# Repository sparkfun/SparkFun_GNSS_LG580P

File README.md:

SparkFun Quadband GNSS RTK with Heading Breakout - LG580P (Qwiic)
========================================

[*SparkFun Quadband GNSS RTK with Heading Breakout - LG580P (Qwiic) (GPS-28019)*](https://www.sparkfun.com/sparkfun-quadband-gnss-rtk-with-heading-breakout-lg580p-qwiic.html)

The [SparkFun Quadband GNSS RTK with Heading Breakout - LG580P (Qwiic)](https://www.sparkfun.com/sparkfun-quadband-gnss-rtk-with-heading-breakout-lg580p-qwiic.html) features the Quectel LG580P GNSS module, providing exceptional positioning and heading accuracy. The LG580P GNSS module is an upgraded version of the LG290P on our [SparkFun Quadband GNSS RTK Breakout - LG290P (Qwiic)](https://www.sparkfun.com/sparkfun-quadband-gnss-rtk-breakout-lg290p-qwiic.html); providing an additional GNSS antenna input for instantaneous heading determination down to 0.1&deg;. In traditional navigation systems, such as those used on your phone or car, previous navigation points are utilized to determine the course heading. This is the reason why the arrow indicator will spin or be oriented in the wrong directions when the navigation system first boots or has been stationary for extended periods of time. However, with the LG580 GNSS module, users are provided with a dedicated heading without relying on previous course data points, magnetometers/compasses, or gyroscopes in IMUs, which can introduce small errors.

The board's dimensions, pin layout, and connectors are similar to our very popular [SparkFun GPS-RTK-SMA Breakout - ZED-F9P (Qwiic)](https://www.sparkfun.com/sparkfun-gps-rtk-sma-breakout-zed-f9p-qwiic.html), featuring a compact design and convenient Qwiic connectors. *(\*Depending on your application, this board could potentially function as a drop-in replacement; users should verify the pin compatibility of this board with their current installation.)* The board also accommodates users with a diverse choice of interfaces including UART, SPI*, I<sup>2</sup>C*, and CAN*. The board has three UART ports, which are accessible through the USB-C connector, BlueSMiRF *(6-pin PTH)* header, and 4-pin locking JST connector. Users can also interface with the board through the 25 PTH pins that are broken out around the edge of the board. For the GNSS antenna(s), SMA antenna connectors are provided on the edge of the board; an optional, secondary antenna can be utilized for heading determination. We also provide two 4-pin JST Qwiic connectors for future use, when the I<sup>2</sup>C feature becomes available for the GNSS module.

The LG580P module is a quad-band, multi-constellation, high-precision, RTK and heading GNSS receiver. The module is capable of simultaneously receiving signals from the `L1`, `L2`, `L5`, and `L6`/`E6` frequency bands of the GPS, GLONASS, Galileo, BDS, QZSS, and NavIC GNSS constellations. In addition, the module supports SBAS augmentation systems (WAAS, EGNOS, BDSBAS, MSAS, GAGAN, KASS, ASECNA, SouthPAN, and SDCM), PPP services* (BDS PPP-B2b, QZSS CLAS, MADOCA-PPP, and Galileo HAS), RTCM, and RTK corrections for precision navigation with a fast convergence time and reliable performance.

The built-in professional-grade interference signal detection and elimination algorithms, effectively mitigate multiple narrow-band interference sources and significantly improve signal reception performance in complex electromagnetic environments. In addition, the RTK and heading algorithms ensure reliable positioning in challenging scenarios such as urban environments and deep tree cover. With its high-precision, low power consumption and a high positioning and heading update rate of up to 20 Hz, this board is ideal for high-precision navigation applications, such as intelligent robots, precision agriculture, ADAS, and autonomous driving.

> [!NOTE]
> `*`: Feature is still under development

> [!IMPORTANT]
> - Currently, only the UART interface is supported by the module. All three UART ports are broken out to the USB-C connector *(via CH342 USB-serial converter)*, 4-pin locking JST connector, and BlueSMiRF 6-pin header.
> - Additionally, the corrections for some of the PPP services may not be implemented yet.

Documentation
--------------

- **[Hookup Guide (mkdocs)](http://docs.sparkfun.com/SparkFun_GNSS_LG580P/)** - A hookup guide for the SparkFun Quadband GNSS RTK Breakout - LG580P breakout board hosted by GitHub pages<br>
   
- [SparkFun LG290P GNSS Arduino Library](https://github.com/sparkfun/SparkFun_LG290P_GNSS_Arduino_Library) - An Arduino library for the LG290P and LGx80P GNSS modules

Repository Contents
-------------------

- **[/docs](/docs/)** - Online documentation files
  - [/assets](/docs/assets/) - Assets files
    - [/3d_model](/docs/assets/3d_model/) - 3D models for the board
    - [/board_files](/docs/assets/board_files/) - Design files for the board
      - [KiCad Design Files](/docs/assets/board_files/kicad_files.zip) (.zip)
      - [Schematic](/docs/assets/board_files/schematic.pdf) (.pdf)
      - [Dimensions](/docs/assets/board_files/dimensions.pdf) (.pdf)
    - [/component_documentation](/docs/assets/component_documentation/) - Datasheets for hardware components
    - [/img/hookup_guide](/docs/assets/img/hookup_guide/) - Images for hookup guide documentation - Hookup guide images for the board
    - /Hardware - Hardware design files (.brd, .sch)
      - /Production - Production files

Product Variants
----------------

- [GPS-28019](https://www.sparkfun.com/sparkfun-quadband-gnss-rtk-with-heading-breakout-lg580p-qwiic.html) - v1.0, Initial Release
- LG290P Variants
  - [GPS-26620](https://www.sparkfun.com/sparkfun-quadband-gnss-rtk-breakout-lg290p-qwiic.html) - SparkFun LG290P Breakout
  - [GPS-26916](https://www.sparkfun.com/sparkfun-rtk-postcard.html) - SparkFun RTK Postcard *(LG290P + ESP32)*

Version History
---------------

- [v10](https://github.com/sparkfun/SparkFun_GNSS_LG580P/releases/tag/v10) - Initial Release

License Information
-------------------

This product is ***open source***!

Please review the [`LICENSE.md`](./LICENSE.md) file for license information.

If you have any questions or concerns about licensing, please contact technical support on our [SparkFun forums](https://forum.sparkfun.com/viewforum.php?f=152).

Distributed as-is; no warranty is given.

- Your friends at SparkFun.

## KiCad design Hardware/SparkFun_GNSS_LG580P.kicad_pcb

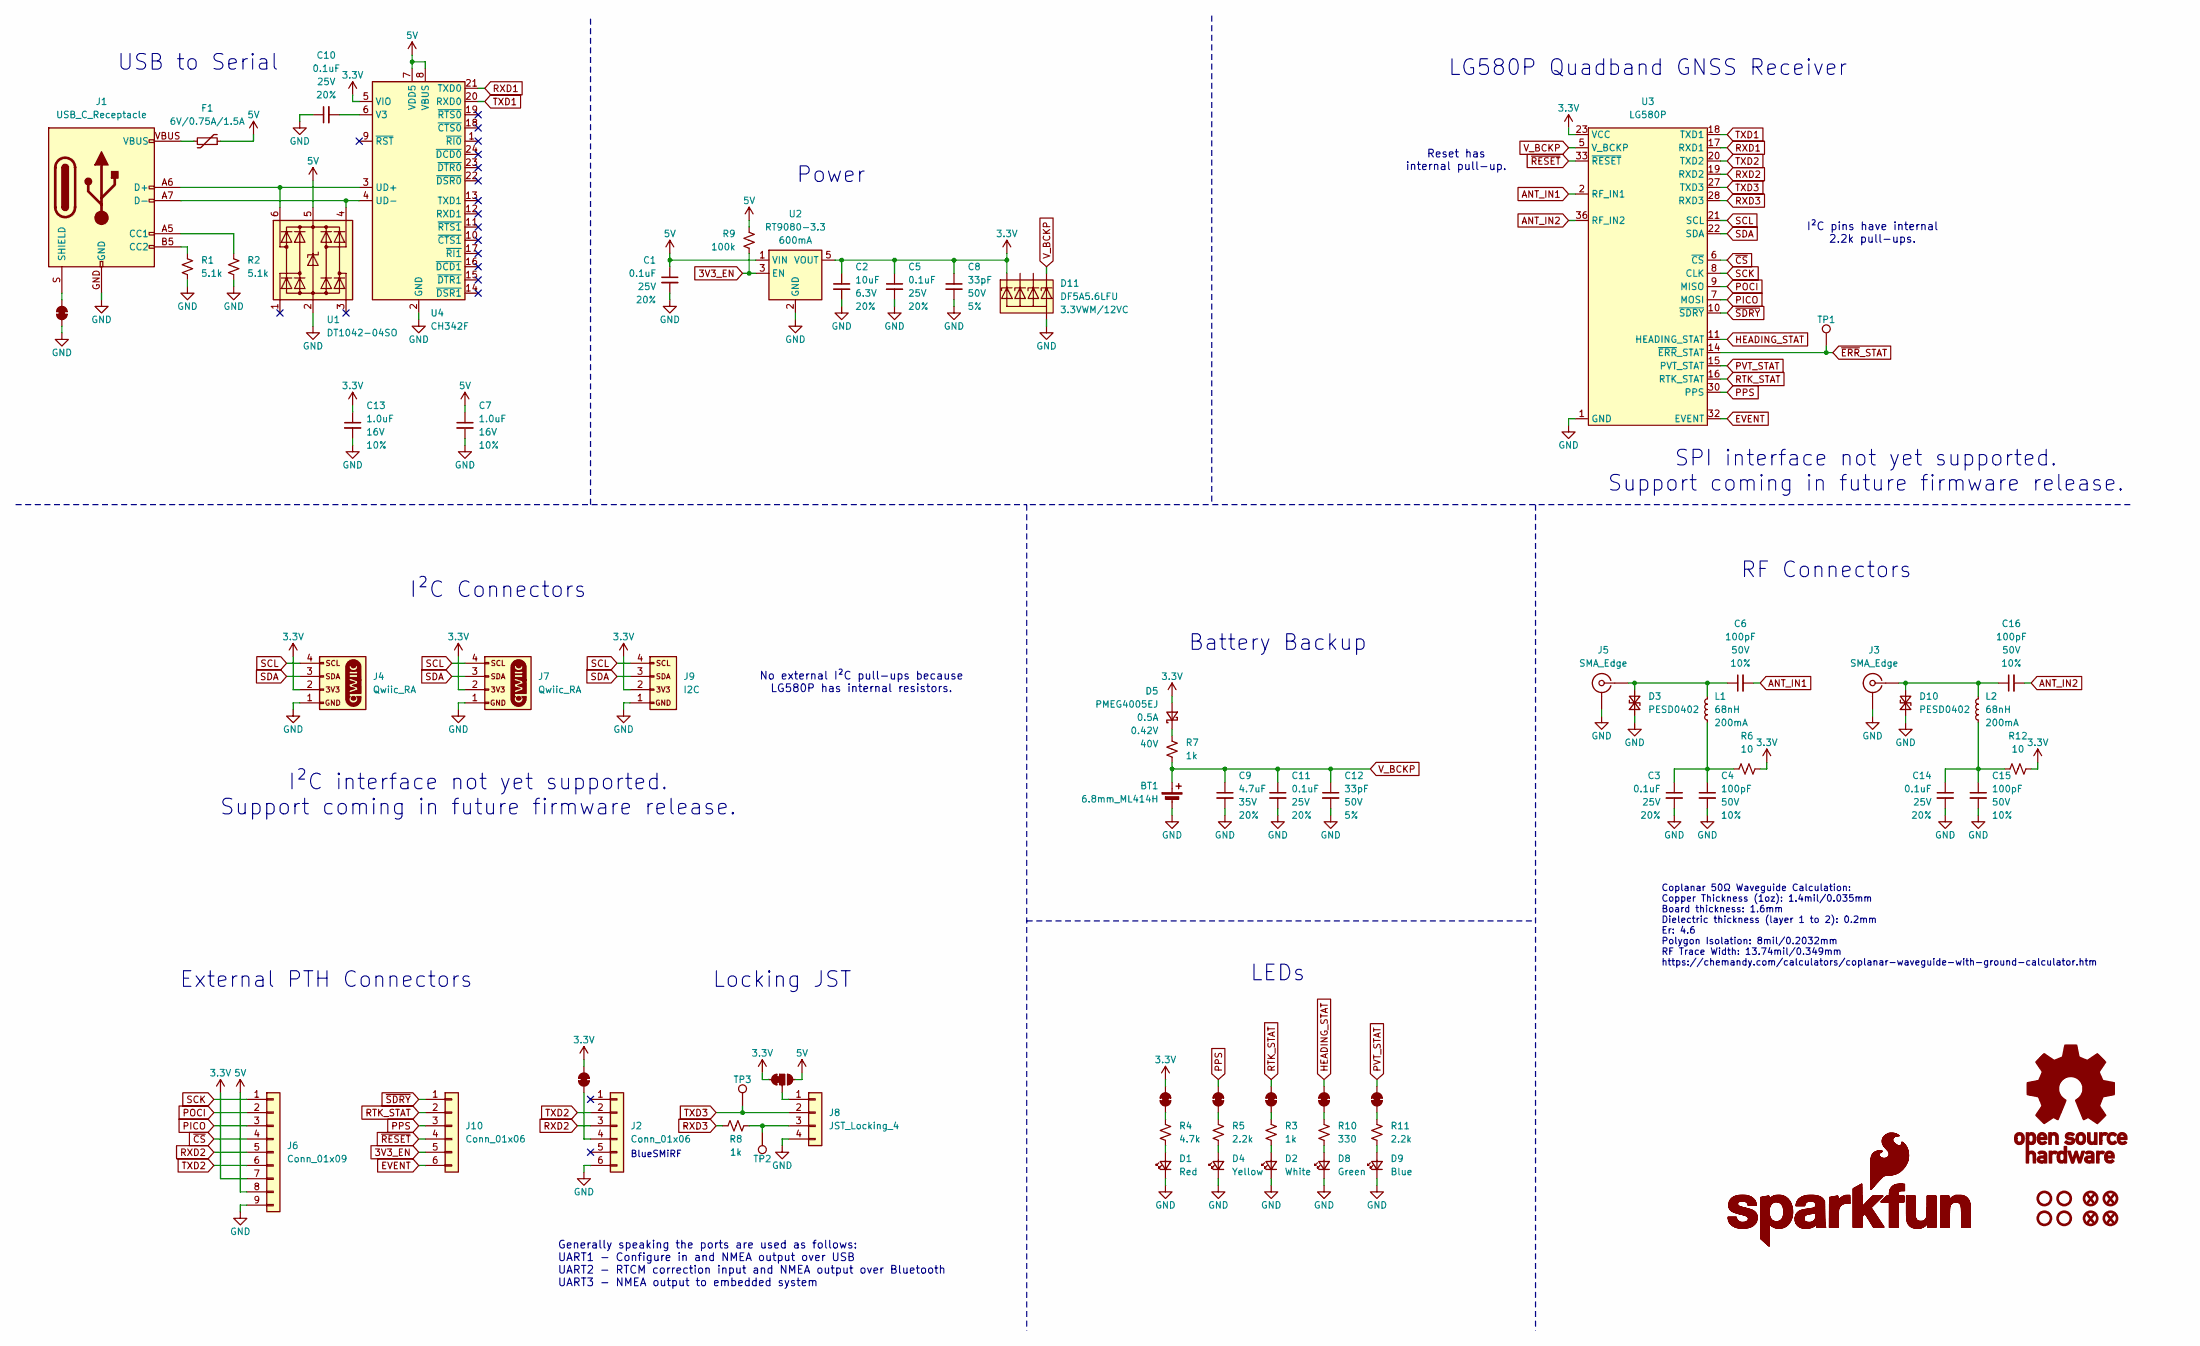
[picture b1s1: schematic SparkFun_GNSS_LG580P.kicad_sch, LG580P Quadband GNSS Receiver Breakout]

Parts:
BT1: 6.8mm_ML414H; ML414H_IV01E
C1, C3, C5, C10, C11, C14: 0.1uF; C_0603_1608Metric; Voltage 25V; Tolerance 20%
C2: 10uF; C_0603_1608Metric; Voltage 6.3V; Tolerance 20%
C4, C15: 100pF; C_0603_1608Metric; Voltage 50V; Tolerance 10%
C6, C16: 100pF; C_0402_1005Metric; Voltage 50V; Tolerance 10%
C7, C13: 1.0uF; C_0603_1608Metric; Voltage 16V; Tolerance 10%
C8, C12: 33pF; C_0603_1608Metric; Voltage 50V; Tolerance 5%
C9: 4.7uF; C_0603_1608Metric; Voltage 35V; Tolerance 20%
D1: Red; LED_0603_1608Metric_Red
D2: White; LED_0603_1608Metric_White
D3, D10: PESD0402; C_0402_1005Metric
D4: Yellow; LED_0603_1608Metric_Yellow
D5: PMEG4005EJ; SOD-323
D8: Green; LED_0603_1608Metric_Green
D9: Blue; LED_0603_1608Metric_Blue
D11: DF5A5.6LFU; SOT-353; Rating 3.3VWM/12VC
F1: 6V/0.75A/1.5A; 1206
FID1, FID2, FID3, FID4: Fiducial_0.5mm; Fiducial_0.5mm_Mask1mm
G1: OSHW_Logo; Creative_Commons_License
G3: SparkFun_Logo
G5: SparkFun_Logo; SparkFun_Logo_8mm
J1: USB_C_Receptacle; USB-C_16
J2, J10: Conn_01x06; 1x06
J3, J5: SMA_Edge
J4, J7: Qwiic_RA; JST_SMD_1.0mm-4_Black
J6: Conn_01x09; 1x09
J8: JST_Locking_4; JST_SMD_1.25mm-4_Locking
J9: I2C; 1x04
JP1, JP2, JP3, JP5, JP6, JP7, JP8: Jumper_2_NC_Trace
JP4: Jumper_3_NC-1_Trace
L1, L2: 68nH; C_0402_1005Metric
R1, R2: 5.1k; R_0603_1608Metric
R3, R7, R8: 1k; R_0603_1608Metric
R4: 4.7k; R_0603_1608Metric
R5, R11: 2.2k; R_0603_1608Metric
R6, R12: 10; R_0603_1608Metric
R9: 100k; R_0603_1608Metric
R10: 330; R_0603_1608Metric
ST1, ST2, ST3, ST4: Standoff
TP1, TP2, TP3: 1.0mm; TestPoint-1.0mm
U1: DT1042-04SO; SOT23-6
U2: RT9080-3.3; SOT23-5
U3: LG580P; Quectel_LG580P
U4: CH342F; QFN-24-1EP_4x4mm_P0.5mm_EP2.7x2.7mm

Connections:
3.3V: C2.1, C5.1, C8.1, C13.1, D5.2 (A), D11.1 (K1), J4.2, J6.7, J7.2, J9.2, JP1.2 (B), JP2.2 (B), JP4.1 (A), R6.2, R12.2, U2.5 (VOUT), U3.23 (VCC), U3.24 (VCC), U4.5 (VIO)
3V3_EN: J10.5, R9.1, U2.3 (EN)
5V: C1.1, C7.1, F1.1, J6.8, JP4.3 (C), R9.2, U1.5 (VCC), U2.1 (VIN), U4.7 (VDD5), U4.8 (VBUS)
ANT_IN1: C6.2, U3.2 (RF_IN1)
ANT_IN2: C16.2, U3.36 (RF_IN2)
EVENT: J10.6, U3.32 (EVENT)
GND: BT1.-, C1.2, C2.2, C3.2, C4.2, C5.2, C7.2, C8.2, C9.2, C10.1, C11.2, C12.2, C13.2, C14.2, C15.2, D1.1 (K), D2.1 (K), D3.1 (A1), D4.1 (K), D8.1 (K), D9.1 (K), D10.1 (A1), D11.2 (A), J1.GND, J2.6, J3.2 (Ext), J4.1, J5.2 (Ext), J6.9, J7.1, J8.4, J9.1, JP7.1 (A), R1.1, R2.1, U1.2 (GND), U2.2 (GND), U3.1 (GND), U3.3 (GND), U3.4 (GND), U3.34 (GND), U3.35 (GND), U3.37 (GND), U3.41 (GND), U3.43 (GND), U3.45 (GND), U3.49 (GND), U4.2 (GND), U4.25 (GND)
HEADING_STAT: JP6.2 (B), U3.11 (HEADING_STAT)
unnamed: C3.1, C4.1, L1.1, R6.1
unnamed: C14.1, C15.1, L2.1, R12.1
unnamed: D1.2 (A), R4.1
unnamed: D2.2 (A), R3.1
unnamed: C6.1, D3.2 (A2), J5.1 (In), L1.2
unnamed: D4.2 (A), R5.1
unnamed: D5.1 (K), R7.2
unnamed: D8.2 (A), R10.1
unnamed: D9.2 (A), R11.1
unnamed: C16.1, D10.2 (A2), J3.1 (In), L2.2
unnamed: F1.2, J1.VBUS
unnamed: J1.A5 (CC1), R2.2
unnamed: J1.B5 (CC2), R1.2
unnamed: J1.S (SHIELD), JP7.2 (B)
unnamed: J2.4, JP1.1 (A)
unnamed: J8.1, JP4.2 (B)
unnamed: J8.3, R8.1, TP2.1
unnamed: JP2.1 (A), R4.2
unnamed: JP3.1 (A), R5.2
unnamed: JP5.1 (A), R3.2
unnamed: JP6.1 (A), R10.2
unnamed: JP8.1 (A), R11.2
unnamed: J1.A7 (D-), J1.B7 (D-), U1.4 (I/O3), U4.4 (UD-)
unnamed: J1.A6 (D+), J1.B6 (D+), U1.6 (I/O4), U4.3 (UD+)
unnamed: C10.2, U4.6 (V3)
PICO: J6.3, U3.7 (MOSI)
POCI: J6.2, U3.9 (MISO)
PPS: J10.3, JP3.2 (B), U3.30 (PPS)
PVT_STAT: JP8.2 (B), U3.15 (PVT_STAT)
RTK_STAT: J10.2, JP5.2 (B), U3.16 (RTK_STAT)
RXD1: U3.17 (RXD1), U4.21 (TXD0)
RXD2: J2.3, J6.5, U3.19 (RXD2)
RXD3: R8.2, U3.28 (RXD3)
SCK: J6.1, U3.8 (CLK)
SCL: J4.4, J7.4, J9.4, U3.21 (SCL)
SDA: J4.3, J7.3, J9.3, U3.22 (SDA)
TXD1: U3.18 (TXD1), U4.20 (RXD0)
TXD2: J2.2, J6.6, U3.20 (TXD2)
TXD3: J8.2, TP3.1, U3.27 (TXD3)
V_BCKP: BT1.+, C9.1, C11.1, C12.1, D11.5 (K4), R7.1, U3.5 (V_BCKP)
~CS: J6.4, U3.6 (~CS)
~ERR_STAT: TP1.1, U3.14 (~ERR_STAT)
~RESET: J10.4, U3.33 (~RESET)
~SDRY: J10.1, U3.10 (~SDRY)

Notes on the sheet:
I²C Connectors
Generally speaking the ports are used as follows: UART1 - Configure in and NMEA output over USB UART2 - RTCM correction input and NMEA output over Bluetooth UART3 - NMEA output to embedded system
Reset has internal pull-up.
I²C interface not yet supported. Support coming in future firmware release.
Coplanar 50Ω Waveguide Calculation: Copper Thickness (1oz): 1.4mil/0.035mm Board thickness: 1.6mm Dielectric thickness (layer 1 to 2): 0.2mm Er: 4.6 Polygon Isolation: 8mil/0.2032mm RF Trace Width: 13.74mil/0.349mm https://chemandy.com/calculators/coplanar-waveguide-with-ground-calculator.htm
I²C pins have internal 2.2k pull-ups.
Locking JST
BlueSMiRF
Power
RF Connectors
LEDs
LG580P Quadband GNSS Receiver
USB to Serial
Battery Backup
SPI interface not yet supported. Support coming in future firmware release.
External PTH Connectors
No external I²C pull-ups because LG580P has internal resistors.

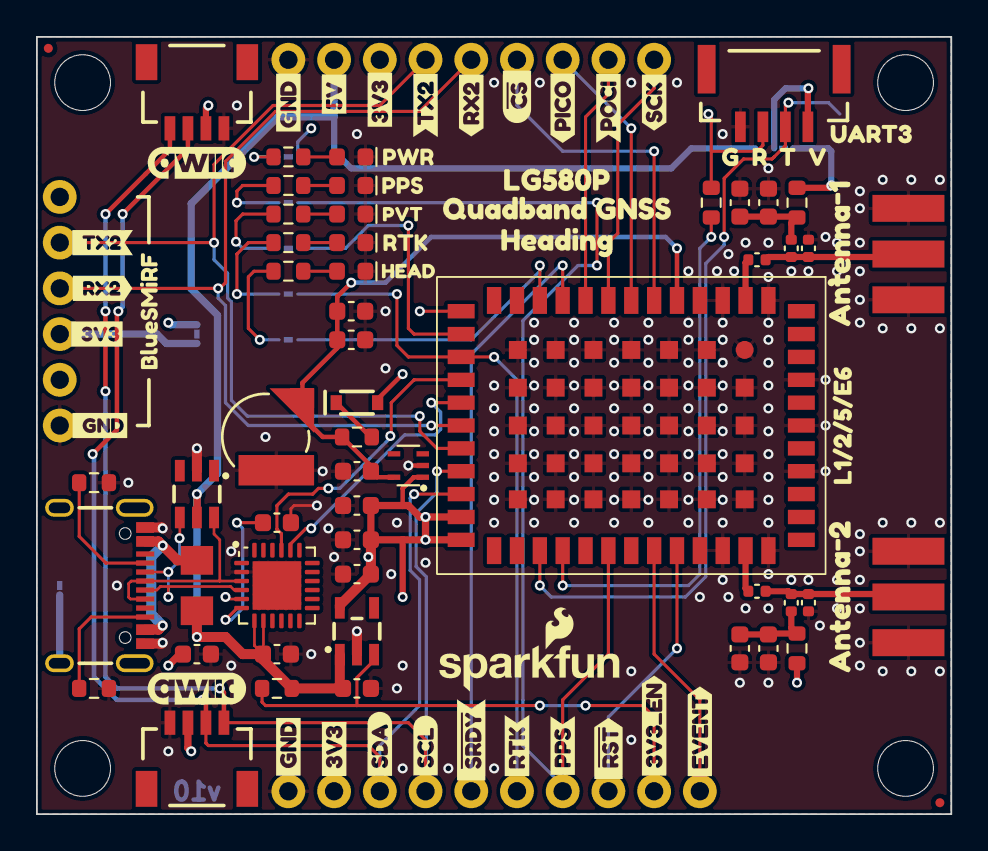
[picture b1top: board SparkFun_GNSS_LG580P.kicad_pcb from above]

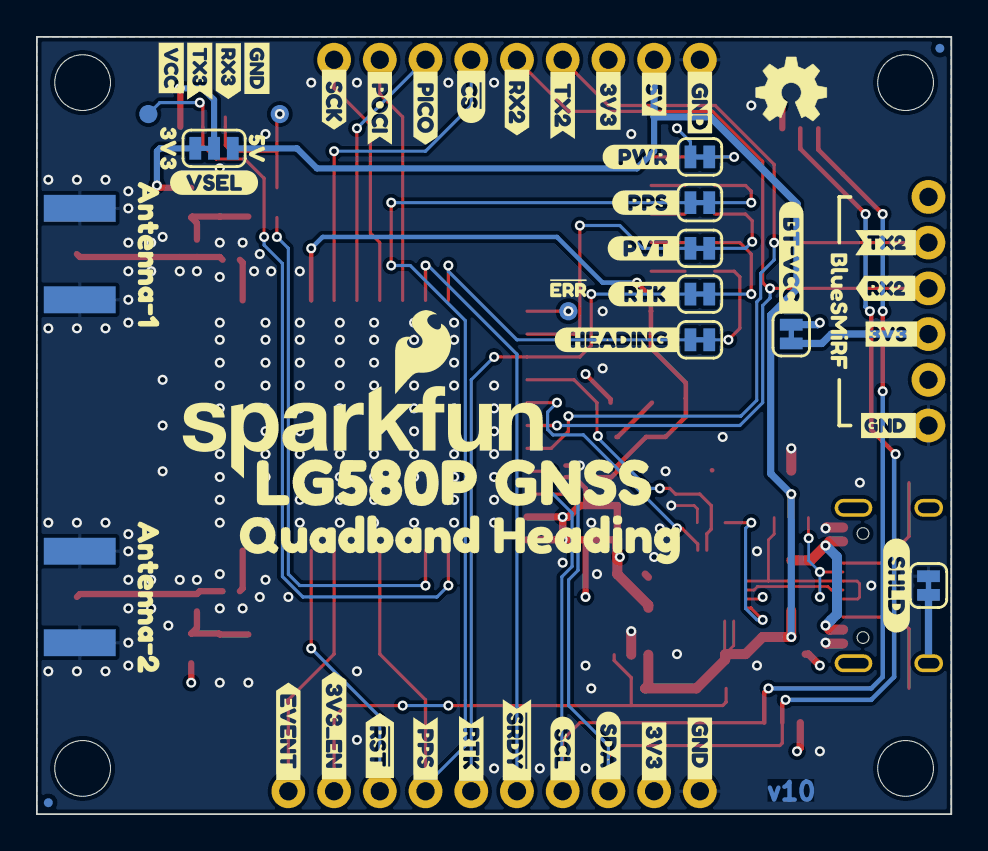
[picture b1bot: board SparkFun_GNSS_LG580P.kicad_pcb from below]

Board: 4 copper layers, 50.8 x 43.2 mm, 156 parts (57 on the bottom side), 52 nets.

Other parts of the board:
Ref**: Val**; OSHW_Logo_4mm
kibuzzard-64C2E6A3: G***; kibuzzard-64C2E6A3
kibuzzard-64C2E6BD: G***; kibuzzard-64C2E6BD
kibuzzard-64C2E6D6: G***; kibuzzard-64C2E6D6
kibuzzard-64C3DF93: G***; kibuzzard-64C3DF93
kibuzzard-66CAA7B2: G***; kibuzzard-66CAA7B2
kibuzzard-66CAA7D2: G***; kibuzzard-66CAA7D2
kibuzzard-66CAA41A: G***; kibuzzard-66CAA41A
kibuzzard-66CAA426: G***; kibuzzard-66CAA426
kibuzzard-66CAA432: G***; kibuzzard-66CAA432
kibuzzard-66CAA594: G***; kibuzzard-66CAA594
kibuzzard-66CB7E2C: G***; kibuzzard-66CB7E2C
kibuzzard-66CB37CC: G***; kibuzzard-66CB37CC
kibuzzard-66CB37D7: G***; kibuzzard-66CB37D7
kibuzzard-66CB82FB: G***; kibuzzard-66CB82FB
kibuzzard-66CB829C: G***; kibuzzard-66CB829C
kibuzzard-66CB830B: G***; kibuzzard-66CB830B
kibuzzard-67A3F35B: G***; kibuzzard-67A3F35B
kibuzzard-67A3F366: G***; kibuzzard-67A3F366
kibuzzard-67C8A377: G***; kibuzzard-67C8A377
kibuzzard-678FE5A2: G***; kibuzzard-678FE5A2
kibuzzard-678FE57D: G***; kibuzzard-678FE57D
kibuzzard-6501FDDA, kibuzzard-6501FDDA#2: G***; kibuzzard-6501FDDA
kibuzzard-6797CCC1: G***; kibuzzard-6797CCC1
kibuzzard-6797CCD8: G***; kibuzzard-6797CCD8
kibuzzard-6797CCDC: G***; kibuzzard-6797CCDC
kibuzzard-6797CD7B: G***; kibuzzard-6797CD7B
kibuzzard-6797CDD0: G***; kibuzzard-6797CDD0
kibuzzard-6797CDE7: G***; kibuzzard-6797CDE7
kibuzzard-6797CDED: G***; kibuzzard-6797CDED
kibuzzard-6797CE3B: G***; kibuzzard-6797CE3B
kibuzzard-6797CE3F: G***; kibuzzard-6797CE3F
kibuzzard-6797CE4B: G***; kibuzzard-6797CE4B
kibuzzard-6797CE44: G***; kibuzzard-6797CE44
kibuzzard-6797CE48: G***; kibuzzard-6797CE48
kibuzzard-6797CEC8, kibuzzard-6797CEC8#2: G***; kibuzzard-6797CEC8
kibuzzard-6797CECC, kibuzzard-6797CECC#2: G***; kibuzzard-6797CECC
kibuzzard-6797CF40: G***; kibuzzard-6797CF40
kibuzzard-6797CFAD: G***; kibuzzard-6797CFAD
kibuzzard-6797CFB3: G***; kibuzzard-6797CFB3
kibuzzard-6797CFD5: G***; kibuzzard-6797CFD5
kibuzzard-6797CFD9: G***; kibuzzard-6797CFD9
kibuzzard-6797CFEB: G***; kibuzzard-6797CFEB
kibuzzard-6797D0AD: G***; kibuzzard-6797D0AD
kibuzzard-6797D0B2: G***; kibuzzard-6797D0B2
kibuzzard-6797D0B5: G***; kibuzzard-6797D0B5
kibuzzard-6797D0B9: G***; kibuzzard-6797D0B9
kibuzzard-6797D0BE: G***; kibuzzard-6797D0BE
kibuzzard-6797D1E0: G***; kibuzzard-6797D1E0
kibuzzard-6797D1F5: G***; kibuzzard-6797D1F5
kibuzzard-6797D2D0: G***; kibuzzard-6797D2D0
kibuzzard-6797D02E: G***; kibuzzard-6797D02E
kibuzzard-6797D04A: G***; kibuzzard-6797D04A
kibuzzard-6797D04F: G***; kibuzzard-6797D04F
kibuzzard-6797D06C: G***; kibuzzard-6797D06C
kibuzzard-6797D07B: G***; kibuzzard-6797D07B
kibuzzard-6797D08B: G***; kibuzzard-6797D08B
kibuzzard-6797D08F: G***; kibuzzard-6797D08F
kibuzzard-6797D021: G***; kibuzzard-6797D021
kibuzzard-6797D21D: G***; kibuzzard-6797D21D
kibuzzard-6797D23B: G***; kibuzzard-6797D23B
kibuzzard-6797D24B: G***; kibuzzard-6797D24B
kibuzzard-6797D025: G***; kibuzzard-6797D025
kibuzzard-6797D029: G***; kibuzzard-6797D029
kibuzzard-6797D30B: G***; kibuzzard-6797D30B
kibuzzard-6797D054: G***; kibuzzard-6797D054
kibuzzard-6797D058: G***; kibuzzard-6797D058
kibuzzard-6797D071: G***; kibuzzard-6797D071
kibuzzard-6797D081: G***; kibuzzard-6797D081
kibuzzard-6797D086: G***; kibuzzard-6797D086
kibuzzard-6797D093: G***; kibuzzard-6797D093
kibuzzard-6797D096: G***; kibuzzard-6797D096
kibuzzard-6797D214: G***; kibuzzard-6797D214
kibuzzard-6797D229: G***; kibuzzard-6797D229
kibuzzard-6797D243: G***; kibuzzard-6797D243
kibuzzard-6797EDFE: G***; kibuzzard-6797EDFE
kibuzzard-6797F4C5: G***; kibuzzard-6797F4C5
kibuzzard-6797F4CD: G***; kibuzzard-6797F4CD

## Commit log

2025-02-06 Post design review changes
2025-02-06 Decrease paste on LG580P FP by 5%
2025-03-05 Adjust values for assembly
2025-04-01 Add panelized files
2025-08-14 Update to KiCad v9
2025-09-12 Remove local FP and symbol
2025-09-22 Initial Docs Setup
2025-09-22 Move files
    Moved component documentation files
2025-09-22 Update footprint
    Updates file path and position of the footprint's 3D model
2025-09-22 Add 3D model files
2025-09-22 Add board files
2025-09-22 Add/Update component documentation
    Added latest datasheets, user manuals, etc.
2025-09-22 Add banner images
2025-09-22 Add Qwiic images
    Adds images for Qwiic connect system
    Add QR code for Qwiic system video
2025-10-06 Update README.md
    Update product description and formatting for the LG580P GNSS module
2025-10-06 Add QR code images
    Added dimension tool, hookup guide, product, and Quectel video images for use in the documentation
2025-10-10 Deployed e901353 with MkDocs version: 1.6.1
2025-10-10 Deployed 5242c3d with MkDocs version: 1.6.1
2025-10-10 Deployed 620b35f with MkDocs version: 1.6.1
2025-10-10 Deployed d91e542 with MkDocs version: 1.6.1
2025-10-10 Initial Docs Commit
    Initial commit for hookup guide files
2025-10-22 Add v05 beta firmware
2025-11-17 Better firmware update instructions
2025-11-17 Deployed 5e8cf1c with MkDocs version: 1.6.1
2025-11-17 Move warning below example
2025-11-17 Deployed 7a17188 with MkDocs version: 1.6.1

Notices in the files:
parts and their libraries:
https://creativecommons.org/licenses/by-sa/4.0
Released under the Creative Commons Attribution Share-Alike 4.0 License
